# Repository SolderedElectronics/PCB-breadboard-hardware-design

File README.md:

# PCB breadboard/protoboard Hardware design

## About the product

|  |
| :----------------------------------------------------------: |
|      [Buy PCB breadboard/protoboard](https://www.solde.red/333031)      |

This PCB is also a breadboard. It offers both the simplicity and the functionality of a breadboard. It is the same size as the modular half-size breadboard and has the same connections to pins. The board allows you to make the temporary circuit from the breadboard permanent.

## Repository contents

All Soldered Electronics hardware designed in KiCAD, and repositories are organized in the following way:

- CAD folder - contains KiCAD files (Schematics, Board, Panel Board), sorted by version. Change log lists all changes between versions.
- OUTPUTS - contains useful files, such as Bill of Materials (BOM), PDF of schematics, 3D .step file of the board and gerber files, sorted by version. 
- OUTPUTS -> Compliance - Certificates and useful legal stuff. 

## Want to contribute?

Please feel free to submit a pull request if you have any contributions. We encourage you to submit an issue or pull request if you find a bug. 

## About Soldered

At Soldered, we design and manufacture a wide selection of electronic products to help you turn your ideas into acts and bring you one step closer to your final project. Our products are intented for makers and crafted in-house by our experienced team in Osijek, Croatia. We believe that sharing is a crucial element for improvement and innovation, and we work hard to stay connected with all our makers regardless of their skill or experience level. Therefore, all our products are open-source. Finally, we always have your back. If you face any problem concerning either your shopping experience or your electronics project, our team will help you deal with it, offering efficient customer service and cost-free technical support anytime. Some of those might be useful for you:

- [Web Store](https://www.soldered.com/shop)
- [Tutorials & Projects](https://soldered.com/learn)
- [Community & Technical support](https://soldered.com/community)

## License info

All Soldered open-source hardware (OSH) is under The TAPR Open Hardware License. Read more in the LICENSE file. 

No warranty - all designs in this repository are distributed in the hope that they will be useful, but without any warranty. They are provided "AS IS", therefore without warranty of any kind, either expressed or implied. The entire quality and performance of what you do with the contents of this repository are your responsibility. In no event, Soldered Electronics will be liable for your damages, losses, including any general, special, incidental or consequential damage arising out of the use or inability to use the contents of this repository. 

## Have fun! 
And thank you from your fellow makers at Soldered Electronics.

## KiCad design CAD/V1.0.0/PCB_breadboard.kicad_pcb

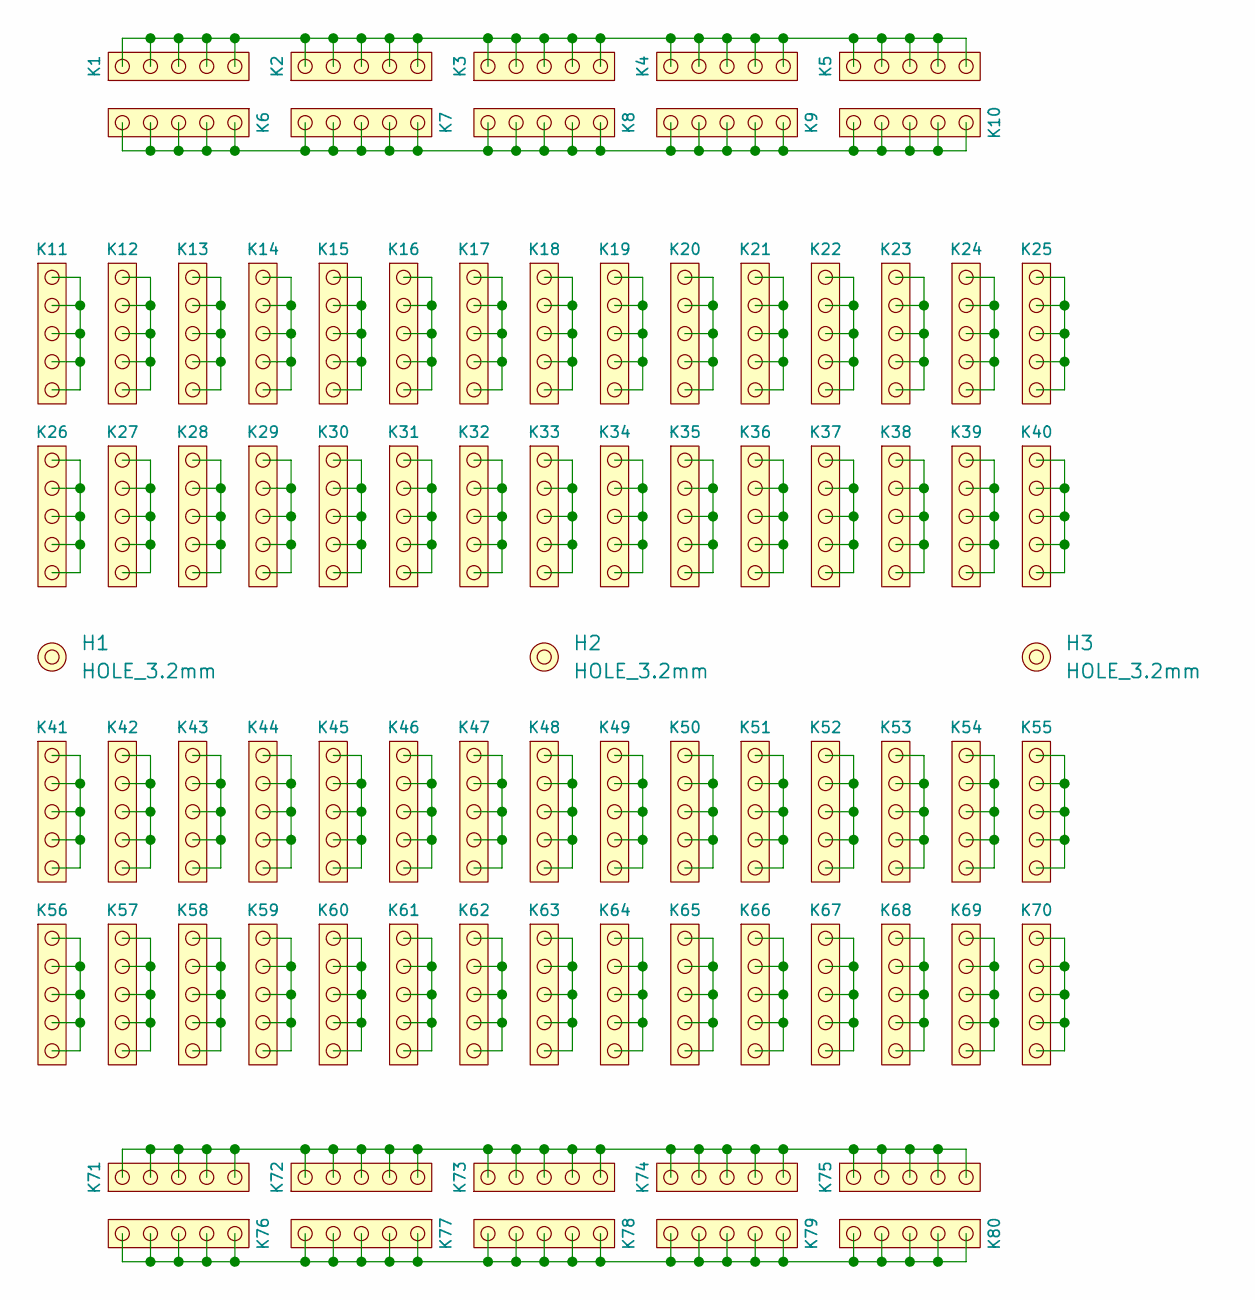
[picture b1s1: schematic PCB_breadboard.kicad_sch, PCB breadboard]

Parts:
H1, H2, H3: HOLE_3.2mm
K1, K2, K3, K4, K5, K6, K7, K8, K9, K10, K11, K12, K13, K14, K15, K16, K17, K18, K19, K20, K21, K22, K23, K24, K25, K26, K27, K28, K29, K30, K31, K32, K33, K34, K35, K36, K37, K38, K39, K40, K41, K42, K43, K44, K45, K46, K47, K48, K49, K50, K51, K52, K53, K54, K55, K56, K57, K58, K59, K60, K61, K62, K63, K64, K65, K66, K67, K68, K69, K70, K71, K72, K73, K74, K75, K76, K77, K78, K79, K80: HEADER_MALE_5X1

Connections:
unnamed: K1.1, K1.2, K1.3, K1.4, K1.5, K2.1, K2.2, K2.3, K2.4, K2.5, K3.1, K3.2, K3.3, K3.4, K3.5, K4.1, K4.2, K4.3, K4.4, K4.5, K5.1, K5.2, K5.3, K5.4, K5.5
unnamed: K6.1, K6.2, K6.3, K6.4, K6.5, K7.1, K7.2, K7.3, K7.4, K7.5, K8.1, K8.2, K8.3, K8.4, K8.5, K9.1, K9.2, K9.3, K9.4, K9.5, K10.1, K10.2, K10.3, K10.4, K10.5
unnamed: K11.1, K11.2, K11.3, K11.4, K11.5
unnamed: K12.1, K12.2, K12.3, K12.4, K12.5
unnamed: K13.1, K13.2, K13.3, K13.4, K13.5
unnamed: K14.1, K14.2, K14.3, K14.4, K14.5
unnamed: K15.1, K15.2, K15.3, K15.4, K15.5
unnamed: K16.1, K16.2, K16.3, K16.4, K16.5
unnamed: K17.1, K17.2, K17.3, K17.4, K17.5
unnamed: K18.1, K18.2, K18.3, K18.4, K18.5
unnamed: K19.1, K19.2, K19.3, K19.4, K19.5
unnamed: K20.1, K20.2, K20.3, K20.4, K20.5
unnamed: K21.1, K21.2, K21.3, K21.4, K21.5
unnamed: K22.1, K22.2, K22.3, K22.4, K22.5
unnamed: K23.1, K23.2, K23.3, K23.4, K23.5
unnamed: K24.1, K24.2, K24.3, K24.4, K24.5
unnamed: K25.1, K25.2, K25.3, K25.4, K25.5
unnamed: K26.1, K26.2, K26.3, K26.4, K26.5
unnamed: K27.1, K27.2, K27.3, K27.4, K27.5
unnamed: K28.1, K28.2, K28.3, K28.4, K28.5
unnamed: K29.1, K29.2, K29.3, K29.4, K29.5
unnamed: K30.1, K30.2, K30.3, K30.4, K30.5
unnamed: K31.1, K31.2, K31.3, K31.4, K31.5
unnamed: K32.1, K32.2, K32.3, K32.4, K32.5
unnamed: K33.1, K33.2, K33.3, K33.4, K33.5
unnamed: K34.1, K34.2, K34.3, K34.4, K34.5
unnamed: K35.1, K35.2, K35.3, K35.4, K35.5
unnamed: K36.1, K36.2, K36.3, K36.4, K36.5
unnamed: K37.1, K37.2, K37.3, K37.4, K37.5
unnamed: K38.1, K38.2, K38.3, K38.4, K38.5
unnamed: K39.1, K39.2, K39.3, K39.4, K39.5
unnamed: K40.1, K40.2, K40.3, K40.4, K40.5
unnamed: K41.1, K41.2, K41.3, K41.4, K41.5
unnamed: K42.1, K42.2, K42.3, K42.4, K42.5
unnamed: K43.1, K43.2, K43.3, K43.4, K43.5
unnamed: K44.1, K44.2, K44.3, K44.4, K44.5
unnamed: K45.1, K45.2, K45.3, K45.4, K45.5
unnamed: K46.1, K46.2, K46.3, K46.4, K46.5
unnamed: K47.1, K47.2, K47.3, K47.4, K47.5
unnamed: K48.1, K48.2, K48.3, K48.4, K48.5
unnamed: K49.1, K49.2, K49.3, K49.4, K49.5
unnamed: K50.1, K50.2, K50.3, K50.4, K50.5
unnamed: K51.1, K51.2, K51.3, K51.4, K51.5
unnamed: K52.1, K52.2, K52.3, K52.4, K52.5
unnamed: K53.1, K53.2, K53.3, K53.4, K53.5
unnamed: K54.1, K54.2, K54.3, K54.4, K54.5
unnamed: K55.1, K55.2, K55.3, K55.4, K55.5
unnamed: K56.1, K56.2, K56.3, K56.4, K56.5
unnamed: K57.1, K57.2, K57.3, K57.4, K57.5
unnamed: K58.1, K58.2, K58.3, K58.4, K58.5
unnamed: K59.1, K59.2, K59.3, K59.4, K59.5
unnamed: K60.1, K60.2, K60.3, K60.4, K60.5
unnamed: K61.1, K61.2, K61.3, K61.4, K61.5
unnamed: K62.1, K62.2, K62.3, K62.4, K62.5
unnamed: K63.1, K63.2, K63.3, K63.4, K63.5
unnamed: K64.1, K64.2, K64.3, K64.4, K64.5
unnamed: K65.1, K65.2, K65.3, K65.4, K65.5
unnamed: K66.1, K66.2, K66.3, K66.4, K66.5
unnamed: K67.1, K67.2, K67.3, K67.4, K67.5
unnamed: K68.1, K68.2, K68.3, K68.4, K68.5
unnamed: K69.1, K69.2, K69.3, K69.4, K69.5
unnamed: K70.1, K70.2, K70.3, K70.4, K70.5
unnamed: K71.1, K71.2, K71.3, K71.4, K71.5, K72.1, K72.2, K72.3, K72.4, K72.5, K73.1, K73.2, K73.3, K73.4, K73.5, K74.1, K74.2, K74.3, K74.4, K74.5, K75.1, K75.2, K75.3, K75.4, K75.5
unnamed: K76.1, K76.2, K76.3, K76.4, K76.5, K77.1, K77.2, K77.3, K77.4, K77.5, K78.1, K78.2, K78.3, K78.4, K78.5, K79.1, K79.2, K79.3, K79.4, K79.5, K80.1, K80.2, K80.3, K80.4, K80.5

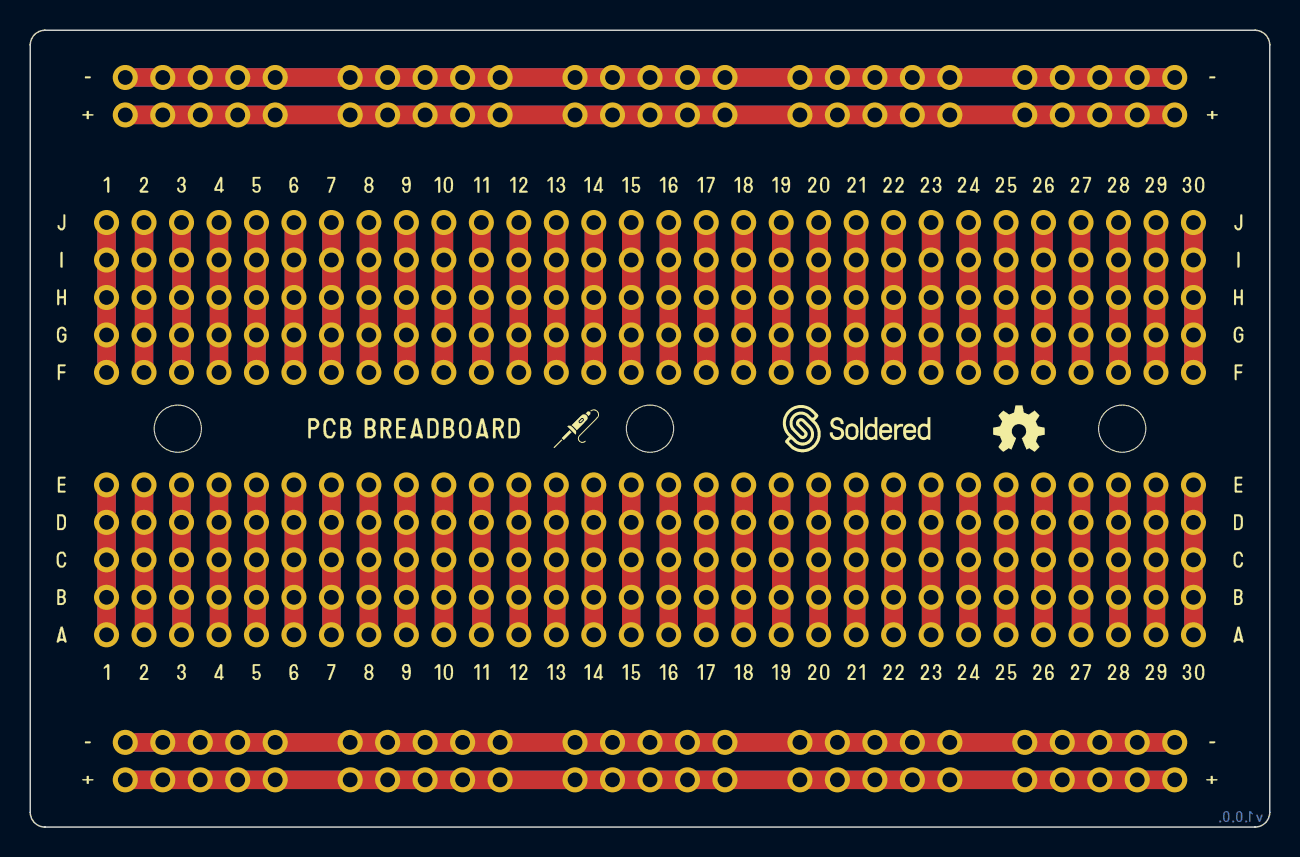
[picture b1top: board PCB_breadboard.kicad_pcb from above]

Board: 2 copper layers, 84.0 x 54.0 mm, 83 parts (0 on the bottom side), 64 nets.

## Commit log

2022-08-06 Updating open source files.
